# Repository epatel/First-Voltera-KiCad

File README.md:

First Voltera KiCad
===================

Here are the project files I produced when trying to create my own PCB from scratch using KiCad.

The goal was to try out the Voltera One I bought via [Kickstarter](https://www.kickstarter.com/projects/voltera/voltera-your-circuit-board-prototyping-machine)

All turned out fine and so far all cards has worked straight out of the machine.

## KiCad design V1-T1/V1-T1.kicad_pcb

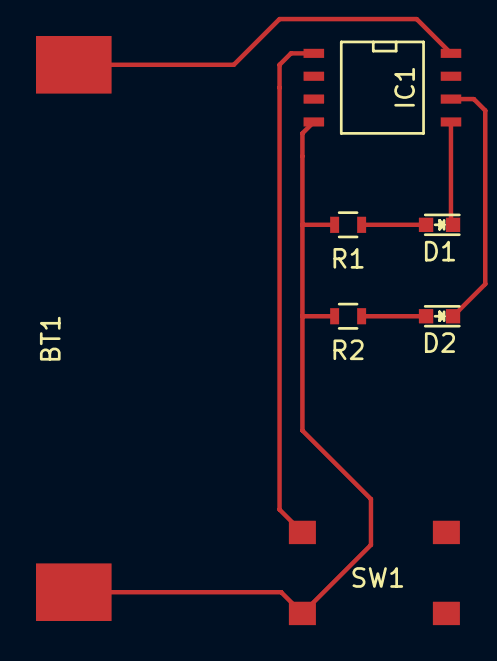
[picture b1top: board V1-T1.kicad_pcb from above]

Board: 2 copper layers, 7 parts (0 on the bottom side), 7 nets.

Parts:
BT1: Battery_Cell; Battery_2032
D1, D2: LED; LED_0603
IC1: attiny85
R1, R2: R; R_0603
SW1: SMDPushButton; Button_SMD_6x6x6

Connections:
unnamed: BT1.1, IC1.8
unnamed: BT1.2, IC1.4, R1.2, R2.2, SW1.3
unnamed: D1.1, IC1.5
unnamed: D1.2, R1.1
unnamed: D2.1, IC1.6
unnamed: D2.2, R2.1
unnamed: IC1.1, SW1.1

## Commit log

2017-01-01 Added plotted Gerber files
2017-01-01 Added photo
2017-01-01 Added attiny85 code
